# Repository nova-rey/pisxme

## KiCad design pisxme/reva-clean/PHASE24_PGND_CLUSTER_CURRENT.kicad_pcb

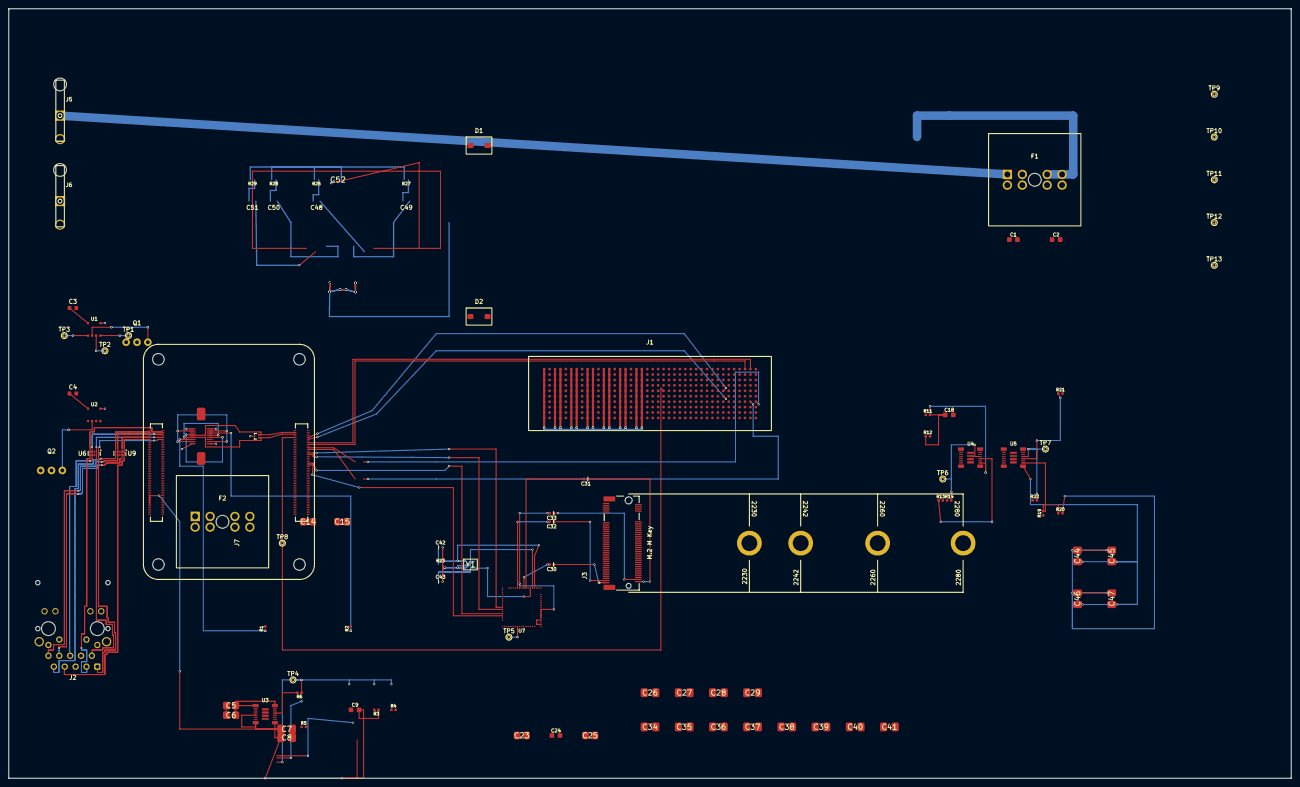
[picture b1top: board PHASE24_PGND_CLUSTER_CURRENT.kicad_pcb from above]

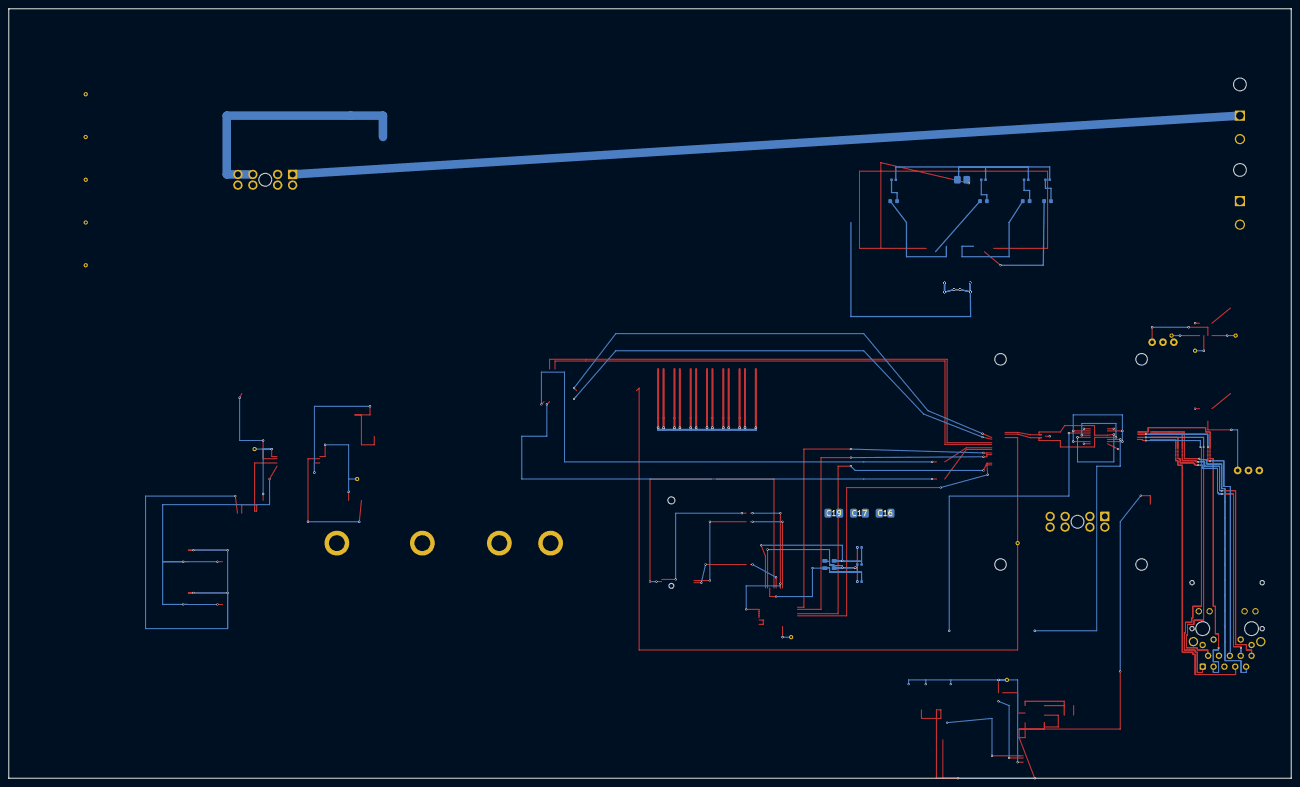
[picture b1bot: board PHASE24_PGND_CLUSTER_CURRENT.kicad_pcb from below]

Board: 6 copper layers, 300.0 x 180.0 mm, 101 parts (27 on the bottom side), 76 nets.

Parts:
C1, C2, C9, C18, C24: C_0805_2012Metric
C3, C4, C48, C49, C50, C51: C_0603_1608Metric
C5, C6, C14, C15, C23, C25, C52: C_1206_3216Metric
C7, C8, C16, C17, C19, C26, C27, C28, C29, C34, C35, C36, C37, C38, C39, C40, C41, C44, C45, C46, C47: C_1210_3225Metric
C30, C31, C32, C33, C42, C43: C_0402_1005Metric
D1, D2: SMBJ18A; TVS_SMBJ18A_DO214AA
F1, F2: 178.6165.0001; ATO_FuseHolder_17861650001
J1: 74221-101LF; PiSXMeRevAClean_SXM2_74221_101LF
J2: A70-112-331N126; EDAC_A70_112_331N126
J3: JAE SM3ZS067U410ABR1000 B-key SATA socket; JAE_SM3ZS067U410ABR1000_BKEY
J4: Amphenol 10171746-00021LF USB-C USB2 SERVICE; USB_C_SERVICE_10171746
J5, J6: 0039300020; Molex_0039300020_5569_2P_RA
J7: Raspberry-Pi-5-Compute-Module; PiSXMeRevAClean_Raspberry_Pi_5_Compute_Module
MECH_M2_2280: JAE SM3ZS067U410ABR1000 / 2280 card envelope; M2_2280_RETENTION_ENVELOPE
Q1, Q2: CSD19536KCS; CSD19536KCS_TO220
R1, R2, R3, R4, R5, R6, R11, R12, R13, R14, R19, R20, R21, R22, R23, R26, R27, R28, R29: R_0402_1005Metric
TP1, TP2, TP3, TP4, TP5, TP6, TP7, TP8, TP9, TP10, TP11, TP12, TP13: REV_A_PROBE; TestPoint_THTPad_D1.0mm_Drill0.5mm
U1, U2: LM74700QDBVRQ1; LM74700QDBVRQ1_SOT23_6
U3, U4, U5: TPSM63606RDLR; TPSM63606RDLR_RDL0020
U6, U9: TPD4EUSB30; USON-10_2.5x1.0mm_P0.5mm
U7: TUSB9261IPVP; TUSB9261IPVP_HTQFP64
U8: Texas_DRT_3
Y1: Crystal_3225_4Pad

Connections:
12V_PROTECTED: C5.1, C6.1, C14.1, C15.1, C23.1, C24.1, C25.1, J1.A22, J1.A23, J1.A25, J1.A26, J1.A28, J1.A29, J1.A31, J1.A32, J1.A34, J1.A35, J1.A37, J1.A38, J1.A40, J1.B22, J1.B23, J1.B25, J1.B26, J1.B28, J1.B29, J1.B31, J1.B32, J1.B34, J1.B35, J1.B37, J1.B38, J1.B40, J1.C22, J1.C23, J1.C25, J1.C26, J1.C28, J1.C29, J1.C31, J1.C32, J1.C34, J1.C35, J1.C37, J1.C38, J1.C40, J1.D22, J1.D23, J1.D25, J1.D26, J1.D28, J1.D29, J1.D31, J1.D32, J1.D34, J1.D35, J1.D37, J1.D38, J1.D40, J1.E22, J1.E23, J1.E25, J1.E26, J1.E28, J1.E29, J1.E31, J1.E32, J1.E34, J1.E35, J1.E37, J1.E38, J1.E40, J1.F22, J1.F23, J1.F25, J1.F26, J1.F28, J1.F29, J1.F31, J1.F32, J1.F34, J1.F35, J1.F37, J1.F38, J1.F40, J1.G22, J1.G23, J1.G25, J1.G26, J1.G28, J1.G29, J1.G31, J1.G32, J1.G34, J1.G35, J1.G37, J1.G38, J1.G40, J1.H22, J1.H23, J1.H25, J1.H26, J1.H28, J1.H29, J1.H31, J1.H32, J1.H34, J1.H35, J1.H37, J1.H38, J1.H40, J1.J22, J1.J23, J1.J25, J1.J26, J1.J28, J1.J29, J1.J31, J1.J32, J1.J34, J1.J35, J1.J37, J1.J38, J1.J40, J1.K22, J1.K23, J1.K25, J1.K26, J1.K28, J1.K29, J1.K31, J1.K32, J1.K34, J1.K35, J1.K37, J1.K38, J1.K40, Q1.2, Q2.2, TP3.1, U1.4, U2.4, U3.1, U3.14, U3.16, U4.1, U4.14, U4.16, U5.1, U5.14, U5.16
/CORE_CM5/CM5_5V: C7.1, C8.1, C9.2, J7.77, J7.79, J7.81, J7.83, J7.85, J7.87, R3.1, R6.1, TP4.1, U3.5, U3.8, U3.9
/CORE_CM5/CM5_PER0_N: J1.A3, J7.118
/CORE_CM5/CM5_PER0_P: J1.A2, J7.116
/CORE_CM5/CM5_PERST: J1.E18, J7.109, TP8.1
/CORE_CM5/CM5_PET0_N: C2.1, J7.124
/CORE_CM5/CM5_PET0_P: C1.1, J7.122
/CORE_CM5/CM5_REFCLK_N: J1.F7, J7.112
/CORE_CM5/CM5_REFCLK_P: J1.E7, J7.110
/CORE_CM5/CM5_USB3_RX_N: J7.128, U7.42
/CORE_CM5/CM5_USB3_RX_P: J7.130, U7.43
/CORE_CM5/CM5_USB3_TX_N: J7.140, U7.45
/CORE_CM5/CM5_USB3_TX_P: J7.142, U7.46
/CORE_CM5/POWER_GND: J7.1, J7.2, J7.7, J7.8, J7.13, J7.14, J7.22, J7.23, J7.32, J7.33, J7.42, J7.43, J7.52, J7.53, J7.59, J7.60, J7.65, J7.66, J7.71, J7.74, J7.98, J7.107, J7.108, J7.113, J7.114, J7.119, J7.120, J7.125, J7.126, J7.131, J7.132, J7.137, J7.138, J7.144, J7.150, J7.155, J7.156, J7.161, J7.162, J7.167, J7.168, J7.173, J7.174, J7.179, J7.180, J7.185, J7.186, J7.191, J7.192, J7.197, J7.198
/CORE_CM5/SERVICE_USB2_DM: J4.A7, J4.B7, J7.103, U8.2
/CORE_CM5/SERVICE_USB2_DP: J4.A6, J4.B6, J7.105, U8.1
/ETHERNET/ETH_CT1: C48.1, J2.11
/ETHERNET/ETH_CT2: C49.1, J2.12
/ETHERNET/ETH_CT3: C50.1, J2.13
/ETHERNET/ETH_CT4: C51.1, J2.14
/ETHERNET/ETH_CT_BRANCH_1: C48.2, R26.1
/ETHERNET/ETH_CT_BRANCH_2: C49.2, R27.1
/ETHERNET/ETH_CT_BRANCH_3: C50.2, R28.1
/ETHERNET/ETH_CT_BRANCH_4: C51.2, R29.1
/ETHERNET/ETH_CT_COMMON: C52.1, R26.2, R27.2, R28.2, R29.2
/ETHERNET/ETH_POWER: J2.15, J2.17
/ETHERNET/GBE_SHIELD: C52.2, J2.19, J2.20
/POWER_INPUT/12V_IN_A: C3.2, F1.1, F1.2, F1.3, F1.4, J5.1, TP1.1, U1.3
/POWER_INPUT/12V_IN_B: C4.2, F2.1, F2.2, F2.3, F2.4, J6.1, U2.3
/POWER_INPUT/FUSED_12V_A: D1.1, F1.5, F1.6, F1.7, F1.8, Q1.1, TP2.1, U1.6
/POWER_INPUT/FUSED_12V_B: D2.1, F2.5, F2.6, F2.7, F2.8, Q2.1, U2.6
/POWER_INPUT/GATE_A: Q1.3, U1.5
/POWER_INPUT/GATE_B: Q2.3, U2.5
/POWER_INPUT/VCAP_A: C3.1, U1.1
/POWER_INPUT/VCAP_B: C4.1, U2.1
/REGULATORS/BRIDGE_1V1: C26.1, C27.1, C28.1, C29.1, C34.1, C35.1, C36.1, C37.1, C38.1, C39.1, C40.1, C41.1, C44.1, C45.1, C46.1, C47.1, R19.1, R22.1, U5.5, U5.8, U5.9
/REGULATORS/BRIDGE_3V3: C16.1, C17.1, C18.2, C19.1, R11.1, R14.1, U4.5, U4.8, U4.9
/REGULATORS/FB_BRIDGE_1V1: R19.2, R20.1, U5.10
/REGULATORS/FB_BRIDGE_3V3: C18.1, R11.2, R12.1, U4.10
/REGULATORS/FB_CM5_5V: C9.1, R3.2, R4.1, U3.10
/REGULATORS/NC: U3.15, U4.15, U5.15
/REGULATORS/PG_BRIDGE_1V1: R22.2, TP7.1, U5.13
/REGULATORS/PG_BRIDGE_3V3: R14.2, TP6.1, U4.13
/REGULATORS/PG_CM5_5V: R6.2, U3.13
/REGULATORS/RT_BRIDGE_1V1: R21.1, U5.12
/REGULATORS/RT_BRIDGE_3V3: R13.1, U4.12
/REGULATORS/RT_CM5_5V: R5.1, U3.12
/SERVICE/SERVICE_RD_A: J4.A5, R1.1
/SERVICE/SERVICE_RD_B: J4.B5, R2.1
/SERVICE/SERVICE_VBUS_SENSE: J4.A4, J4.A9, J4.B4, J4.B9
/STORAGE/BRIDGE_1V1: U7.3, U7.41
/STORAGE/BRIDGE_3V3: TP5.1, U7.24, U7.30, U7.31
/STORAGE/BRIDGE_CFG: U7.1, U7.21
/STORAGE/BRIDGE_RESET: U7.2, U7.4
/STORAGE/BRIDGE_SATA_RX_N: C33.2, U7.5, U7.6, U7.7, U7.8, U7.9, U7.59
/STORAGE/BRIDGE_SATA_RX_P: C32.2, U7.60
/STORAGE/BRIDGE_SATA_TX_N: C31.2, U7.56
/STORAGE/BRIDGE_SATA_TX_P: C30.2, U7.57
/STORAGE/BRIDGE_VSSOSC: C42.2, C43.2, U7.53, Y1.2, Y1.4
/STORAGE/BRIDGE_XI: C42.1, R23.1, U7.52, Y1.1
/STORAGE/BRIDGE_XO: C43.1, R23.2, U7.54, Y1.3
/STORAGE/SATA_M2_RX_N: C33.1, J3.4
/STORAGE/SATA_M2_RX_P: C32.1, J3.3
/STORAGE/SATA_M2_TX_N: C31.1, J3.2
/STORAGE/SATA_M2_TX_P: C30.1, J3.1
/V100_PCIE/V100_PET0_N: C2.2, J1.G2
/V100_PCIE/V100_PET0_P: C1.2, J1.G1
CM5_GBE_TD0_N: J2.2, J7.10, U6.2 (D1-), U6.9
CM5_GBE_TD0_P: J2.1, J7.12, U6.1 (D1+), U6.10
CM5_GBE_TD1_N: J2.6, J7.6, U6.4 (D2+), U6.7
CM5_GBE_TD1_P: J2.3, J7.4, U6.5 (D2-), U6.6
CM5_GBE_TD2_N: J2.8, J7.9, U9.2 (D1-), U9.9
CM5_GBE_TD2_P: J2.7, J7.11, U9.1 (D1+), U9.10
CM5_GBE_TD3_N: J2.10, J7.5, U9.4 (D2+), U9.7
CM5_GBE_TD3_P: J2.9, J7.3, U9.5 (D2-), U9.6
POWER_GND: C5.2, C6.2, C7.2, C8.2, C14.2, C15.2, C16.2, C17.2, C19.2, C23.2, C24.2, C25.2, C26.2, C27.2, C28.2, C29.2, C34.2, C35.2, C36.2, C37.2, C38.2, C39.2, C40.2, C41.2, C44.2, C45.2, C46.2, C47.2, D1.2, D2.2, J1.A21, J1.A24, J1.A27, J1.A30, J1.A33, J1.A36, J1.A39, J1.B21, J1.B24, J1.B27, J1.B30, J1.B33, J1.B36, J1.B39, J1.C21, J1.C24, J1.C27, J1.C30, J1.C33, J1.C36, J1.C39, J1.D21, J1.D24, J1.D27, J1.D30, J1.D33, J1.D36, J1.D39, J1.E21, J1.E24, J1.E27, J1.E30, J1.E33, J1.E36, J1.E39, J1.F21, J1.F24, J1.F27, J1.F30, J1.F33, J1.F36, J1.F39, J1.G21, J1.G24, J1.G27, J1.G30, J1.G33, J1.G36, J1.G39, J1.H21, J1.H24, J1.H27, J1.H30, J1.H33, J1.H36, J1.H39, J1.J21, J1.J24, J1.J27, J1.J30, J1.J33, J1.J36, J1.J39, J1.K21, J1.K24, J1.K27, J1.K30, J1.K33, J1.K36, J1.K39, J3.6, J4.A1, J4.A12, J4.B1, J4.B12, J5.2, J6.2, R1.2, R2.2, R4.2, R5.2, R12.2, R13.2, R20.2, R21.2, TP9.1, U1.2, U2.2, U3.6, U3.11, U3.17, U3.18, U3.19, U3.20, U4.6, U4.11, U4.17, U4.18, U4.19, U4.20, U5.6, U5.11, U5.17, U5.18, U5.19, U5.20, U6.3 (GND), U6.8 (GND), U8.3, U9.3 (GND), U9.8 (GND)

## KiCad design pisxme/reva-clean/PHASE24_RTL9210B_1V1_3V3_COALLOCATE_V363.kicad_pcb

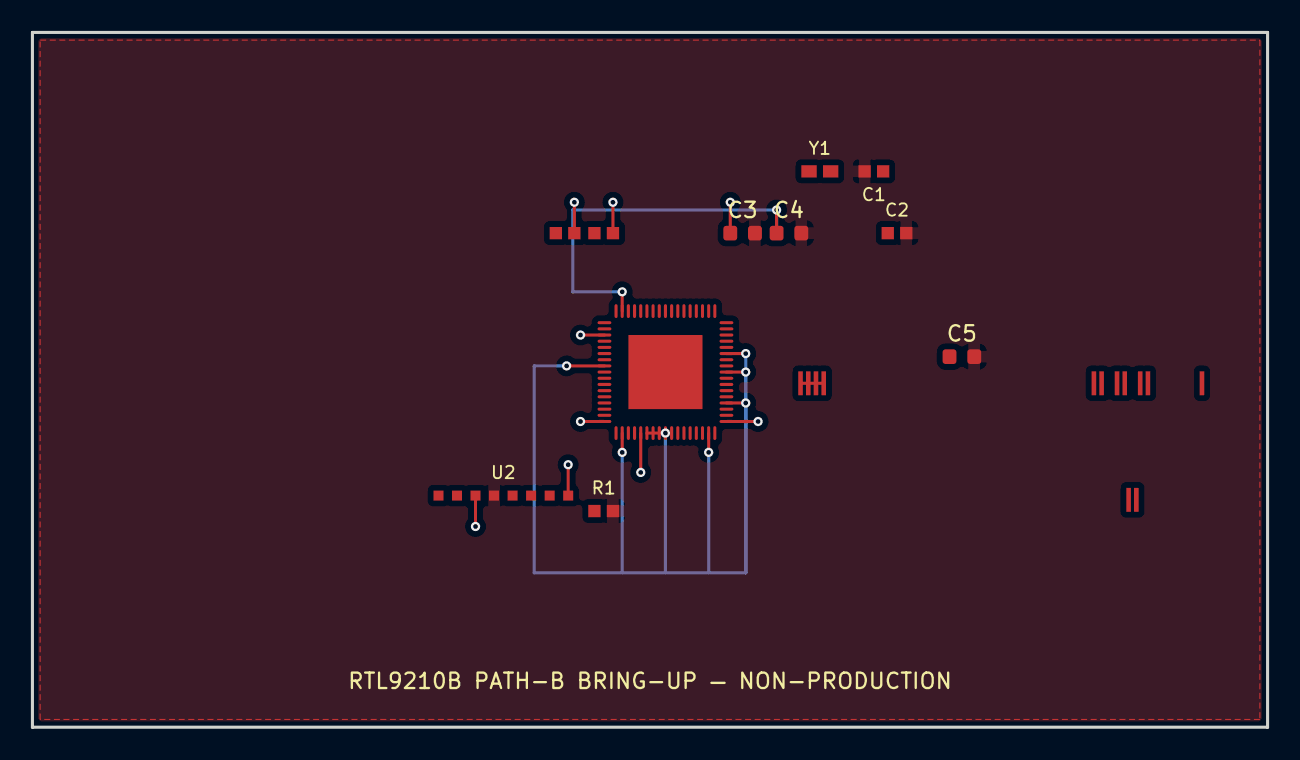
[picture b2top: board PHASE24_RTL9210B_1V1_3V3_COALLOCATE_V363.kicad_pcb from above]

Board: 6 copper layers, 80.0 x 45.0 mm, 12 parts (0 on the bottom side), 22 nets.

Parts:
C1: 16pF_XTAL_IN; BRINGUP_16pF_XTAL_IN
C2: 16pF_XTAL_OUT; BRINGUP_16pF_XTAL_OUT
C3, C4, C5: C_0603_1608Metric
J1: M.2 Socket 3 M-key 2280; BRINGUP_M2_MKEY
R1: 12k_RSET; BRINGUP_12k_RSET
R2: PEDET_PULLUP; BRINGUP_PEDET_PULLUP
R3: CLKREQ_PULLUP; BRINGUP_CLKREQ_PULLUP
U1: RTL9210B-CG; RTL9210B-CG_QUALIFICATION
U2: W25Q128_SPI_FLASH; BRINGUP_W25Q128_SPI_FLASH
Y1: XTAL_25MHz; BRINGUP_XTAL_25MHz

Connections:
CLKREQ_N: J1.52, R3.1, U1.13
GND: C1.2, C2.2, C3.2, C4.2, C5.2, R1.2, U1.45, U1.66, U1.69, U2.4
LANE0_RXN: J1.41, U1.65
LANE0_RXP: J1.43, U1.64
LANE0_TXN: J1.47, U1.67
LANE0_TXP: J1.49, U1.68
PEDET: J1.69, R2.1, U1.8
PERST_N: J1.50, U1.14
REFCLK_N: J1.53, U1.62
REFCLK_P: J1.55, U1.61
RSET: R1.1, U1.51
RTL_1V1: C4.1, U1.16, U1.25, U1.36, U1.40, U1.50, U1.55, U1.60, U1.63
RTL_3V3: C3.1, R2.2, R3.2, U1.20, U1.34, U1.39, U1.52, U2.3, U2.8
RTL_5V: C5.1, U1.17, U1.33
SPICLK: U1.19, U2.6
SPICS: U1.24, U2.1
SPISI: U1.18, U2.5
SPISO: U1.23, U2.2
SPISO3: U1.22, U2.7
SSD_3V3: J1.2, J1.4, J1.6, J1.8
XTAL_IN: C1.1, U1.53, Y1.1
XTAL_OUT: C2.1, U1.54, Y1.2
